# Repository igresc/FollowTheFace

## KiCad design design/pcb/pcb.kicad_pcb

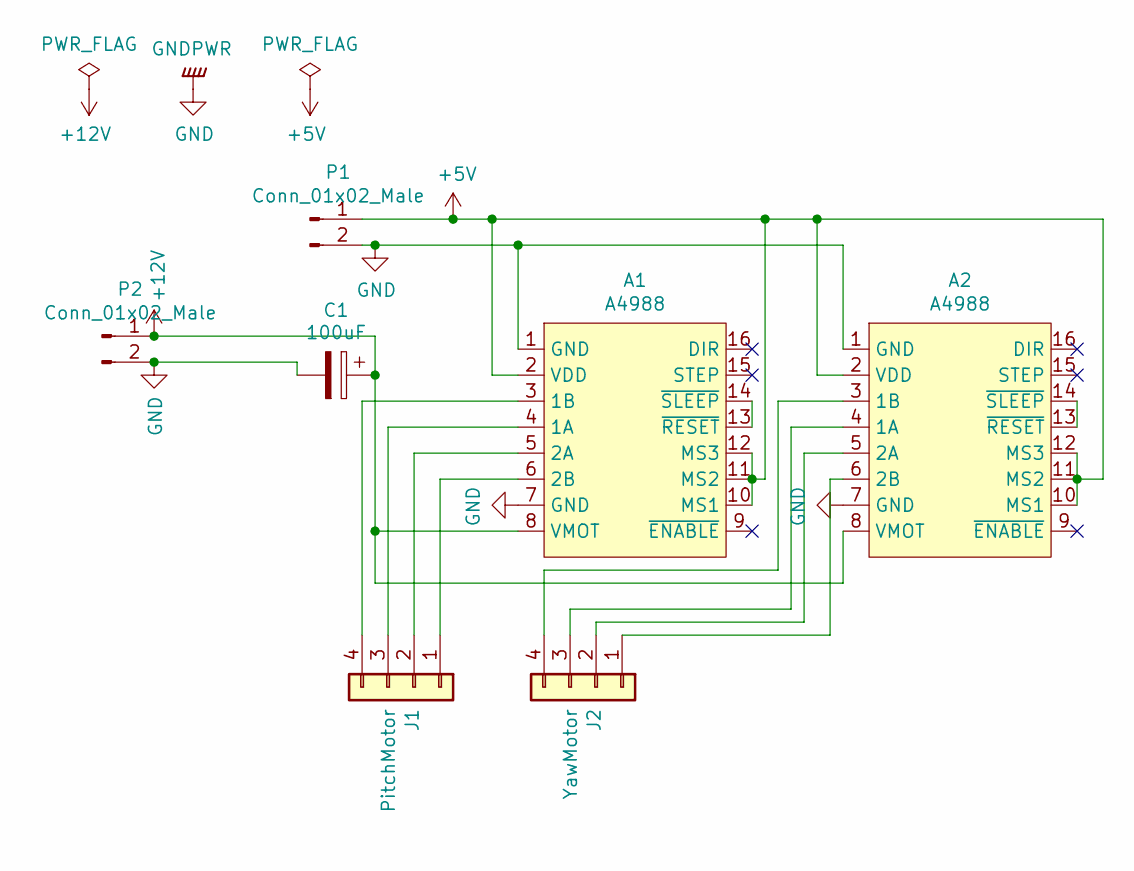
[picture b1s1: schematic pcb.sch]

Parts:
A1, A2: A4988; Pololu_Breakout-16_15.2x20.3mm
C1: 100uF; CP_Radial_D6.3mm_P2.50mm
J1: PitchMotor; PinSocket_1x04_P2.00mm_Vertical
J2: YawMotor; PinSocket_1x04_P2.00mm_Vertical
P1, P2: Conn_01x02_Male; PinHeader_1x02_P2.00mm_Vertical

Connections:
+5V: A1.2 (VDD), A1.10 (MS1), A1.11 (MS2), A1.12 (MS3), A2.2 (VDD), A2.10 (MS1), A2.11 (MS2), A2.12 (MS3), P1.1
+12V: A1.8 (VMOT), A2.8 (VMOT), C1.1, P2.1
GND: A1.1 (GND), A1.7 (GND), A2.1 (GND), A2.7 (GND), C1.2, P1.2, P2.2
unnamed: A1.3 (1B), J1.4
unnamed: A1.4 (1A), J1.3
unnamed: A1.5 (2A), J1.2
unnamed: A1.6 (2B), J1.1
unnamed: A1.13 (~RESET), A1.14 (~SLEEP)
unnamed: A2.3 (1B), J2.4
unnamed: A2.4 (1A), J2.3
unnamed: A2.5 (2A), J2.2
unnamed: A2.6 (2B), J2.1
unnamed: A2.13 (~RESET), A2.14 (~SLEEP)

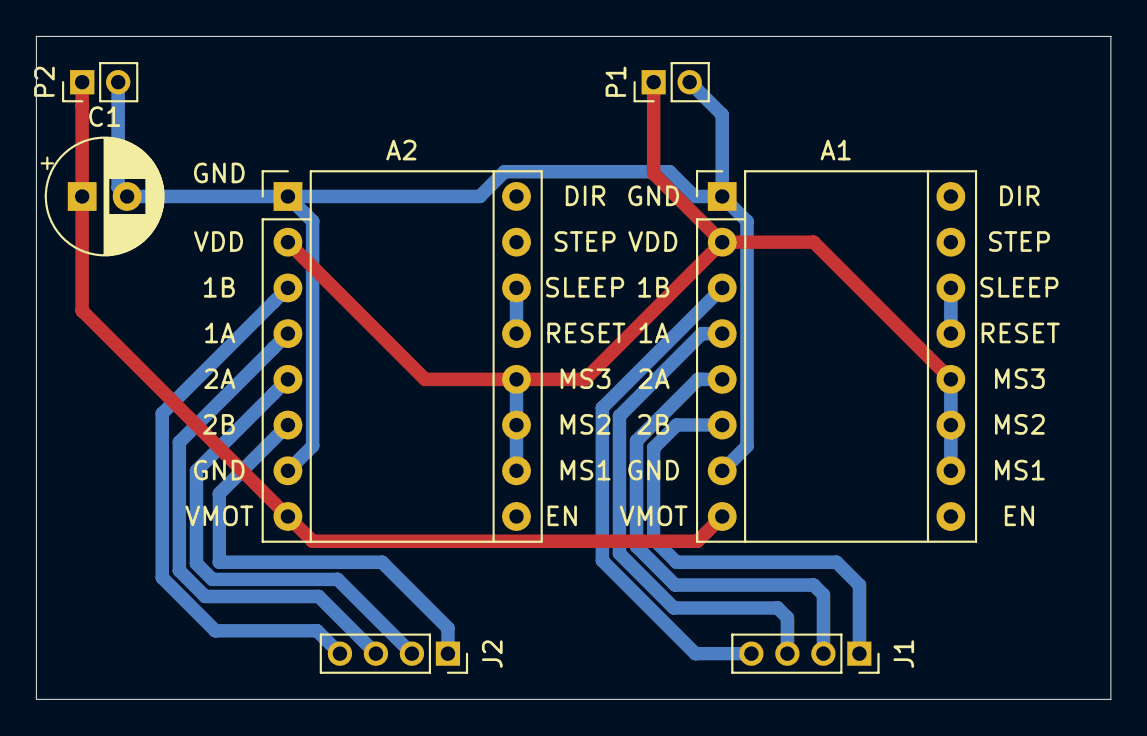
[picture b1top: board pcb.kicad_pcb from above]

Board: 2 copper layers, 59.7 x 36.8 mm, 7 parts (0 on the bottom side), 13 nets.
